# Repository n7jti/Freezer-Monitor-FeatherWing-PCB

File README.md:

# Freezer-Monitor-FeatherWing-PCB
A custom FeatherWing to monitor my freezer door and text me if it is left open.

Code for this based on the Feather Huzzah is found here: https://github.com/n7jti/Arduino/tree/master/FreezerDoorMonitor

This board as been tested and works (not necessarily with the same code) with the following Adafruit Feathers:
* Feather Huzzah: https://www.adafruit.com/product/2821
* WICED Feather: https://www.adafruit.com/product/3056

I'm also working on an AmazonIoT version of the software on the WICED, but that comes later. 

Additionally, this is based on work done by Adafruit: Adafruit invests time and resources that supports this open source design, Please support Adafuit
and open-source hardare by purchasing by purchasing products from Adafruit!

## Parts List:
* Green LED: https://www.adafruit.com/product/844
* Red LED: https://www.adafruit.com/product/845
* R1, R2: 560 Ohm 1/4 watt 5%. (For example: Newark Part Number: 58K5062 Or Digikey: CF14JT560RCT-ND) You could even try (https://www.adafruit.com/product/2781)
* SP1: https://www.adafruit.com/product/160
* Terminal Block: https://www.adafruit.com/product/724
* feather headers: https://www.adafruit.com/product/3002
* Door Sensor: https://www.adafruit.com/product/375

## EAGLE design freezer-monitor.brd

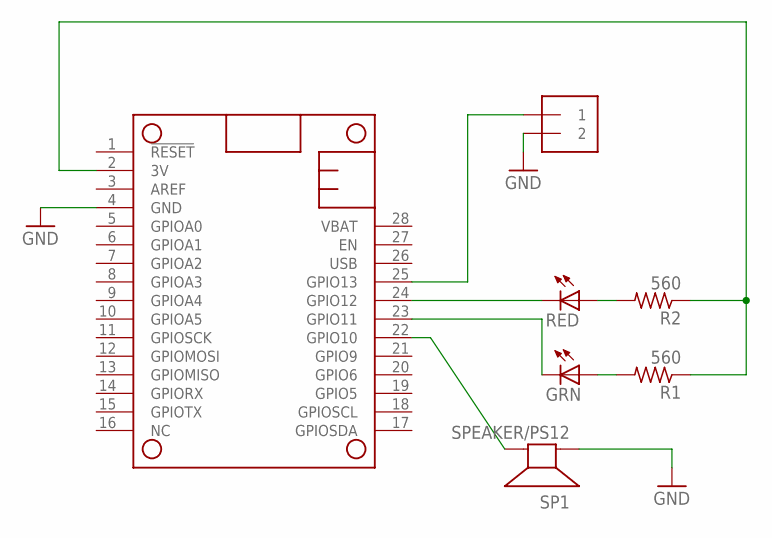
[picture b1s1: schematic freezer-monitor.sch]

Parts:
GRN: LED10MM
J1: 1X2-3.5MM
MS1: FEATHERWING
R1, R2: 560; 0207/10
RED: LED10MM
SP1: SPEAKER/PS12; PS12

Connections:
3V: MS1.2 (3V), R1.1, R2.1
GND: J1.2, MS1.4 (GND), SP1.P$1 (+)
unnamed: MS1.24 (GPIO12), RED.K (C)
unnamed: GRN.A, R1.2
unnamed: J1.1, MS1.25 (GPIO13)
unnamed: R2.2, RED.A
unnamed: GRN.K (C), MS1.23 (GPIO11)
unnamed: MS1.22 (GPIO10), SP1.P$2 (-)

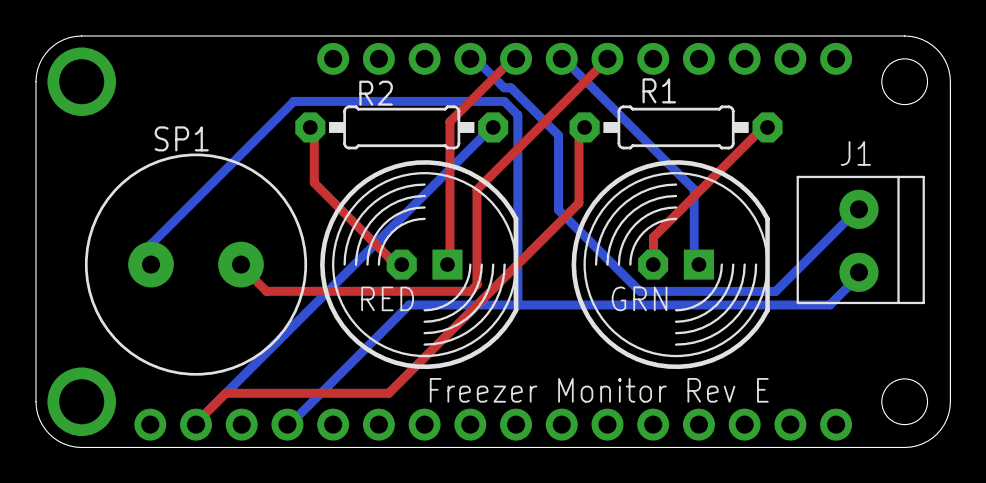
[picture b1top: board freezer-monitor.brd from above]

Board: 2 copper layers, 50.8 x 22.9 mm, 7 parts (0 on the bottom side), 8 nets.

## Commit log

2018-09-03 Checkin REV-E
    REV-E
2018-09-04 Parts List
    Add parts list
2018-09-04 Add door sensor
2018-09-17 Add line from USB to logic in
    Update to bring power from USB port to logic in. This so we can add the ability to text when the power is out.
2018-12-01 Revert "Add line from USB to logic in"
    This reverts commit aa022d101621f46ab4c7c753449e8c0f6e997a72.
